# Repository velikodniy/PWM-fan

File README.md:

# Регулятор оборотов венитилятора

Основан на схеме из статьи [«ШИМ регулятор на таймере NE555»](http://easyelectronics.ru/shim-regulyator-na-tajmere-ne555.html).

Схема спроектирована в САПР KiCAD.

Компоненты:

- Таймер NE555 в корпусе SOIC-8.
- Транзистор 2N7002.
- Резистор на 91 Ω.
- Резистор на 8200 Ω.
- Резистор на 680 Ω.
- Конденсатор на 1 нФ.
- Конденсатор на 2.2 нФ.
- Диод × 3 — любые маломощные.

Все SMD-компоненты размера 1206. Диоды выводные, но использован поверхностный монтаж.

Схема подключается к:

- источнику питания (12 В, можно меньше),
- вентилятору (хорошо работает с вентилятором от блока питания),
- переменному резистору на 5—50 kΩ (средний вывод — бегунок).

Ни один компонент не должен греться во время работы. Частоты ультразвукове, поэтому ШИМ-регулятор не должен быть слышен. Если брать потенциометр с большим сопротивлением, возможно, придётся уменьшить ёмкость C1 для повышения частоты.

## Пути улучшения

Схему можно сделать намного более компактной, разместив компоненты ближе друг к другу и использовав размер 0805.

## Фото собранной схемы

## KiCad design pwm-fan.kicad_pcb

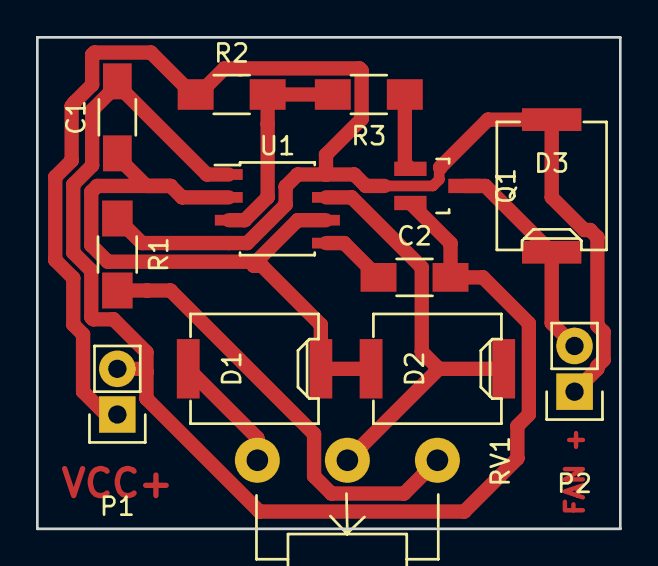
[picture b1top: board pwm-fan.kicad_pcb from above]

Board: 2 copper layers, 32.4 x 27.3 mm, 13 parts (0 on the bottom side), 10 nets.

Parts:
C1: 2.2n; C_1206_HandSoldering
C2: 1n; C_1206_HandSoldering
D1, D2, D3: D; SMD-4032
P1, P2: CONN_01X02; Pin_Header_Straight_1x02
Q1: 2N7002; SOT-23_Handsoldering
R1: 680; R_1206_HandSoldering
R2: 8.2k; R_1206_HandSoldering
R3: 91; R_1206_HandSoldering
RV1: 10k; Potentiometer_WirePads_largePads
U1: NE555; SOIC-8_3.9x4.9mm_Pitch1.27mm

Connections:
GND: C1.2, C2.2, P1.2, Q1.2, U1.1
unnamed: C1.1, D1.2, D2.1, U1.2, U1.6
unnamed: C2.1, U1.5
unnamed: D1.1, RV1.3
unnamed: D2.2, RV1.2, U1.7
unnamed: D3.2, P2.2, Q1.3
unnamed: Q1.1, R3.1
unnamed: R1.2, RV1.1
unnamed: R2.2, R3.2, U1.3
VCC: D3.1, P1.1, P2.1, R1.1, R2.1, U1.4, U1.8

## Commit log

2017-01-03 Add schematics
2017-01-03 Add a photo of PCB
2017-01-03 Add PDFs
2017-01-03 Fix typo
